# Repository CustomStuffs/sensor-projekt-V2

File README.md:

# Sensor Hub

Outdoor environmental monitoring system built on a Raspberry Pi Pico W. Sensors are read every 30 minutes, uploaded over WiFi to a FastAPI server running on a Raspberry Pi, and displayed in a browser dashboard.

## System overview

```
Pico W (MicroPython)
  └─ POST JSON ──► RPi FastAPI server (port 8080)
                      └─ SQLite DB
                      └─ Static files ──► Browser dashboard
```

Remote access via Tailscale VPN — no port forwarding, no auth layer needed.

## Sensors

| Sensor | Chip / interface | Board connection | Measures |
|--------|-----------------|------------------|----------|
| Temperature | DS18B20, 1-Wire (GP8) | W1 (J2) | °C |
| Humidity | DHT22, GP9 | W2 (J3) | % RH + °C fallback |
| pH | AD8603 buffer → ADS1115 AIN0 (I2C, GP2/3) | BNC (J1), guarded input | pH 0–14 |
| Light | VEML7700, I2C (GP2/3) | on the board, under a light pipe to the lid | lux |
| Soil moisture | Capacitive, Pico ADC (GP26) | J11 solder holes (GP26–28) | % |
| Motion | PIR, GP11 (also wake IRQ), power-gated by GP12 | W3 (J4) | boolean |
| Water level | Float switch, GP16 | W4 (J5) | float |
| Probe temperature | NTC → ADS1115 AIN1 | J8 pins 3/4 | °C (for compensation) |
| EC | **not on the v1 board** (LMP91200 is EOL; firmware driver exists, keep `ec` disabled) | — | µS/cm |

All sensor fields are nullable — unconnected sensors send `null`.

## Relays (two on-board channels)

The PCB carries **two independent SPDT relays** (K1 on GP10, K2 on GP15), rated 230 VAC / 5 A with reinforced insulation to the sensor side, as a hard minimum. Both relays can be switched and scheduled from the dashboard, and local sensor rules can target either one (`"relay": 2` in a rule; default is relay 1). This allows two simultaneous actuator channels (e.g. pump + valve) without external modules. Future board variants can add more relays.

- **Auto rules**: threshold-based (e.g. water when soil < 30 %) configured in `firmware/src/config.json`
- **Schedule**: time-based rules, also in `config.json`
- **Manual override**: one-click from the dashboard, queued via server command API

## Repo layout

```
firmware/   MicroPython source + flash/dev tools
server/     FastAPI app, SQLite schema, systemd unit
dashboard/  Vanilla HTML/JS/CSS frontend
hardware/   KiCad project + generation scripts, BOM, JLCPCB order files
```

Each folder has its own `CLAUDE.md` with subproject-specific rules.

## Getting started

### Firmware

Requires MicroPython 1.28+ (`RPI_PICO_W` build).

```bash
cd firmware
bash tools/setup.sh          # install mpremote, check device
cp src/config.json.example src/config.json   # fill in WiFi + server URL
bash tools/flash.sh          # copy all files to device
bash tools/monitor.sh        # watch serial output
```

For daily development, use the mount workflow instead of reflashing:

```bash
bash tools/mount.sh   # edits in src/ take effect on Ctrl-D
```

### Server

```bash
cd server
pip install -r requirements.txt
uvicorn api.main:app --host 0.0.0.0 --port 8080
```

Or run as a systemd service:

```bash
sudo cp sensor_hub.service /etc/systemd/system/
sudo systemctl enable --now sensor_hub
```

### Dashboard

Served as static files by the FastAPI server — no build step. Open `http://<pi-ip>:8080` in a browser.

### Hardware

100 × 100 mm, 2-layer PCB (`hardware/kicad/`), generated and routed by the scripts in `hardware/tools/`. JLCPCB fabricates the board and places all SMD parts (`hardware/fab/`, regenerate with `python3 hardware/tools/jlc_export.py`); the through-hole parts — Pico WH sockets, relays, Wago push-in terminals, BNC, X2 capacitors, UART header — are hand-soldered. Details: `hardware/CLAUDE.md` and `hardware/docs/`.

## Pico W hardware notes

- **VSYS ADC**: use `ADC(29)` (GPIO29), not `ADC(3)`. On Pico W, GPIO29 is the VSYS/3 voltage divider. `ADC(3)` reads GPIO3 (I2C SCL) and gives garbage.
- **VSYS measurement timing**: read VSYS *before* `wlan.active(True)` — GPIO29 is shared with the WiFi SPI bus and returns wrong values while the radio is up.
- **Lightsleep after WiFi**: `machine.lightsleep(ms)` can fail silently on Pico W after WiFi use. The firmware falls back to `time.sleep()` automatically and logs when this happens.
- **Serial monitor**: uses `mpremote` (`bash tools/monitor.sh`), not minicom. On immutable distros (Bazzite/Silverblue), minicom is not available.
- **Flashing**: the device enters lightsleep ~30 s after boot, making `mpremote` unreachable. Flash immediately after plugging in USB, or interrupt via REPL first.

## Power budget (battery operation)

| State | Current |
|-------|---------|
| Lightsleep | 0.30 mA |
| Sensing (all sensors) | 25 mA |
| WiFi active | 80 mA |
| **Average (30 min cycle)** | **~1.2 mA** |

A 10 000 mAh power bank lasts roughly 6–11 months.

## License

MIT

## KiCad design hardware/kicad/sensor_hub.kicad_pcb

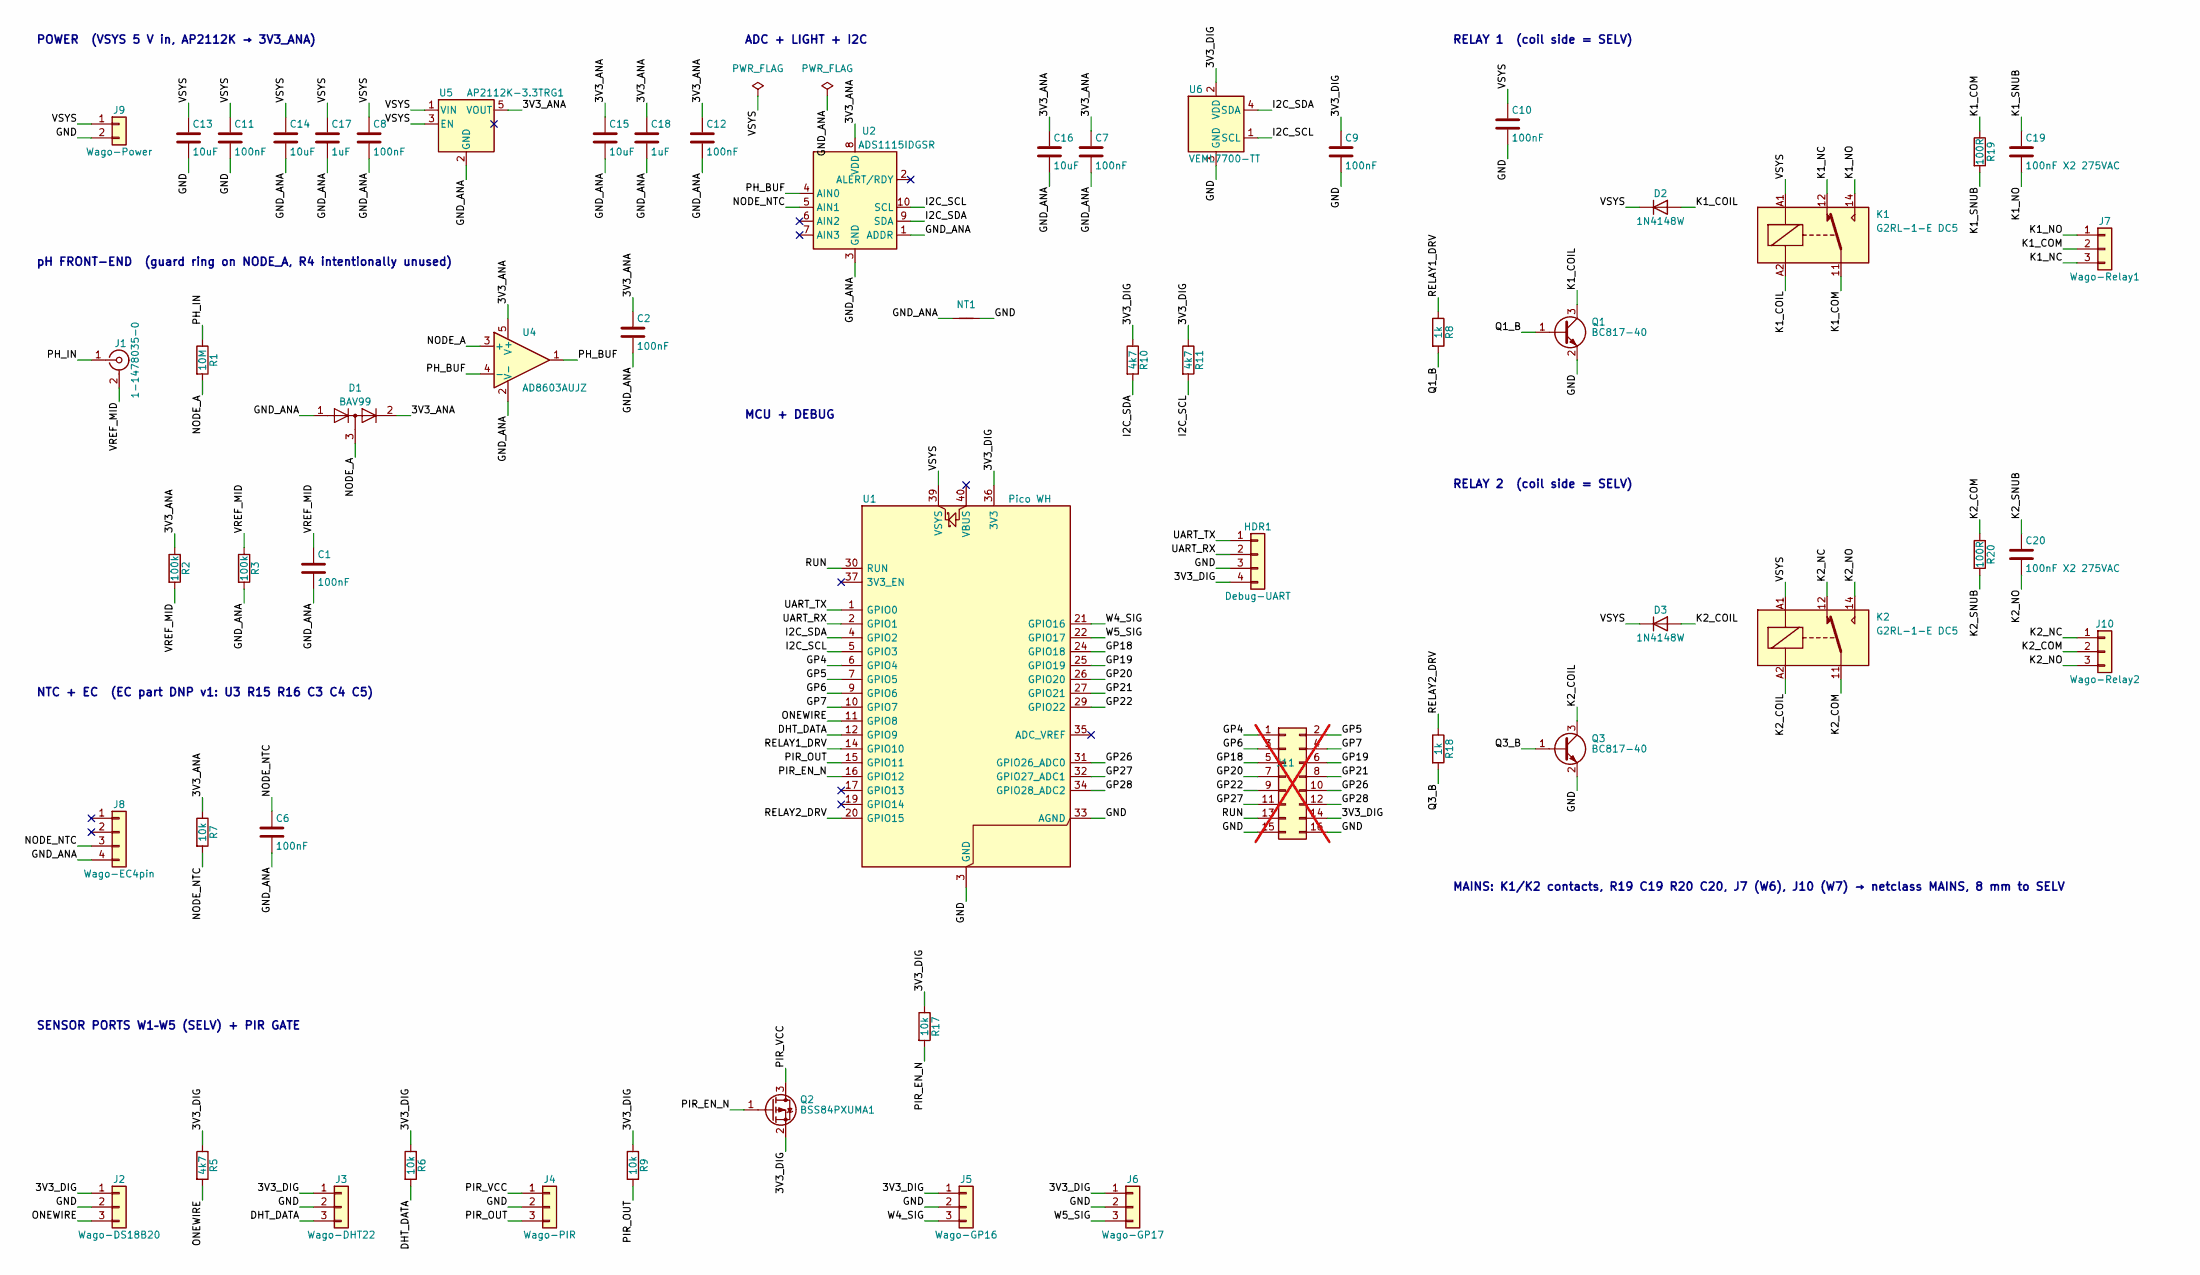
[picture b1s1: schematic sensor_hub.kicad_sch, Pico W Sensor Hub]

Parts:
C1, C2, C6, C7, C8, C9, C10, C11, C12: 100nF; C_0603_1608Metric
C13, C14, C15, C16: 10uF; C_0805_2012Metric
C17, C18: 1uF; C_0603_1608Metric
C19, C20: 100nF X2 275VAC; C_Rect_L13.0mm_W6.0mm_P10.00mm_FKS3_FKP3_MKS4
D1: BAV99; SOT-23
D2, D3: 1N4148W; D_SOD-123
HDR1: Debug-UART; PinHeader_1x04_P2.54mm_Vertical
J1: 1-1478035-0; BNC_TEConnectivity_1478035_Horizontal
J2: Wago-DS18B20; TerminalBlock_WAGO_2601-1103_1x03_P3.50mm_Horizontal
J3: Wago-DHT22; TerminalBlock_WAGO_2601-1103_1x03_P3.50mm_Horizontal
J4: Wago-PIR; TerminalBlock_WAGO_2601-1103_1x03_P3.50mm_Horizontal
J5: Wago-GP16; TerminalBlock_WAGO_2601-1103_1x03_P3.50mm_Horizontal
J6: Wago-GP17; TerminalBlock_WAGO_2601-1103_1x03_P3.50mm_Horizontal
J7: Wago-Relay1; TerminalBlock_WAGO_236-403_1x03_P5.00mm_45Degree
J8: Wago-EC4pin; TerminalBlock_WAGO_2601-1104_1x04_P3.50mm_Horizontal
J9: Wago-Power; TerminalBlock_WAGO_2601-1102_1x02_P3.50mm_Horizontal
J10: Wago-Relay2; TerminalBlock_WAGO_236-403_1x03_P5.00mm_45Degree
J11: Spare-GPIO; PinHeader_2x08_P2.54mm_Vertical; not fitted
K1, K2: G2RL-1-E DC5; Relay_SPDT_Omron_G2RL-1-E
NT1: NetTie_2; NetTie-2_SMD_Pad0.5mm
Q1, Q3: BC817-40; SOT-23
Q2: BSS84PXUMA1; SOT-23
R1: 10M; R_0603_1608Metric
R2, R3: 100k; R_0603_1608Metric
R5, R10, R11: 4k7; R_0603_1608Metric
R6, R7, R9, R17: 10k; R_0603_1608Metric
R8, R18: 1k; R_0603_1608Metric
R19, R20: 100R; R_1206_3216Metric
U1: Pico WH; RaspberryPi_Pico_Common_THT
U2: ADS1115IDGSR; MSOP-10_3x3mm_P0.5mm
U4: AD8603AUJZ; TSOT-23-5
U5: AP2112K-3.3TRG1; SOT-23-5
U6: VEML7700-TT; VEML7700_TT

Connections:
/3V3_ANA: C2.1, C7.1, C12.1, C15.1, C16.1, C18.1, D1.2 (A), R2.1, R7.1, U2.8 (VDD), U4.5 (V+), U5.5 (VOUT)
/3V3_DIG: C9.1, HDR1.4, J2.1, J3.1, J5.1, J6.1, J11.14, Q2.2 (S), R5.1, R6.1, R9.1, R10.1, R11.1, R17.1, U1.36 (3V3), U6.2 (VDD)
/DHT_DATA: J3.3, R6.2, U1.12 (GPIO9)
/GND: C9.2, C10.2, C11.2, C13.2, HDR1.3, J2.2, J3.2, J4.2, J5.2, J6.2, J9.2, J11.15, J11.16, NT1.2, Q1.2 (E), Q3.2 (E), U1.3 (GND), U1.8 (GND), U1.13 (GND), U1.18 (GND), U1.23 (GND), U1.28 (GND), U1.33 (AGND), U1.38 (GND), U6.3 (GND)
/GND_ANA: C1.2, C2.2, C6.2, C7.2, C8.2, C12.2, C14.2, C15.2, C16.2, C17.2, C18.2, D1.1 (K), J8.4, NT1.1, R3.2, U2.1 (ADDR), U2.3 (GND), U4.2 (V-), U5.2 (GND)
/GP4: J11.1, U1.6 (GPIO4)
/GP5: J11.2, U1.7 (GPIO5)
/GP6: J11.3, U1.9 (GPIO6)
/GP7: J11.4, U1.10 (GPIO7)
/GP18: J11.5, U1.24 (GPIO18)
/GP19: J11.6, U1.25 (GPIO19)
/GP20: J11.7, U1.26 (GPIO20)
/GP21: J11.8, U1.27 (GPIO21)
/GP22: J11.9, U1.29 (GPIO22)
/GP26: J11.10, U1.31 (GPIO26_ADC0)
/GP27: J11.11, U1.32 (GPIO27_ADC1)
/GP28: J11.12, U1.34 (GPIO28_ADC2)
/I2C_SCL: R11.2, U1.5 (GPIO3), U2.10 (SCL), U6.1 (SCL)
/I2C_SDA: R10.2, U1.4 (GPIO2), U2.9 (SDA), U6.4 (SDA)
/K1_COIL: D2.2 (A), K1.A2, Q1.3 (C)
/K1_COM: J7.2, K1.11, R19.1
/K1_NC: J7.3, K1.12
/K1_NO: C19.2, J7.1, K1.14
/K1_SNUB: C19.1, R19.2
/K2_COIL: D3.2 (A), K2.A2, Q3.3 (C)
/K2_COM: J10.2, K2.11, R20.1
/K2_NC: J10.1, K2.12
/K2_NO: C20.2, J10.3, K2.14
/K2_SNUB: C20.1, R20.2
/NODE_A: D1.3 (K), R1.2, U4.3 (+)
/NODE_NTC: C6.1, J8.3, R7.2, U2.5 (AIN1)
/ONEWIRE: J2.3, R5.2, U1.11 (GPIO8)
/PH_BUF: U2.4 (AIN0), U4.1, U4.4 (-)
/PH_IN: J1.1 (In), R1.1
/PIR_EN_N: Q2.1 (G), R17.2, U1.16 (GPIO12)
/PIR_OUT: J4.3, R9.2, U1.15 (GPIO11)
/PIR_VCC: J4.1, Q2.3 (D)
/Q1_B: Q1.1 (B), R8.2
/Q3_B: Q3.1 (B), R18.2
/RELAY1_DRV: R8.1, U1.14 (GPIO10)
/RELAY2_DRV: R18.1, U1.20 (GPIO15)
/RUN: J11.13, U1.30 (RUN)
/UART_RX: HDR1.2, U1.2 (GPIO1)
/UART_TX: HDR1.1, U1.1 (GPIO0)
/VREF_MID: C1.1, J1.2 (Ext), R2.2, R3.1
/VSYS: C8.1, C10.1, C11.1, C13.1, C14.1, C17.1, D2.1 (K), D3.1 (K), J9.1, K1.A1, K2.A1, U1.39 (VSYS), U5.1 (VIN), U5.3 (EN)
/W4_SIG: J5.3, U1.21 (GPIO16)
/W5_SIG: J6.3, U1.22 (GPIO17)

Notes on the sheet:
RELAY 1 (coil side = SELV)
ADC + LIGHT + I2C
MCU + DEBUG
NTC + EC (EC part DNP v1: U3 R15 R16 C3 C4 C5)
SENSOR PORTS W1–W5 (SELV) + PIR GATE
pH FRONT-END (guard ring on NODE_A, R4 intentionally unused)
RELAY 2 (coil side = SELV)
MAINS: K1/K2 contacts, R19 C19 R20 C20, J7 (W6), J10 (W7) → netclass MAINS, 8 mm to SELV
POWER (VSYS 5 V in, AP2112K → 3V3_ANA)

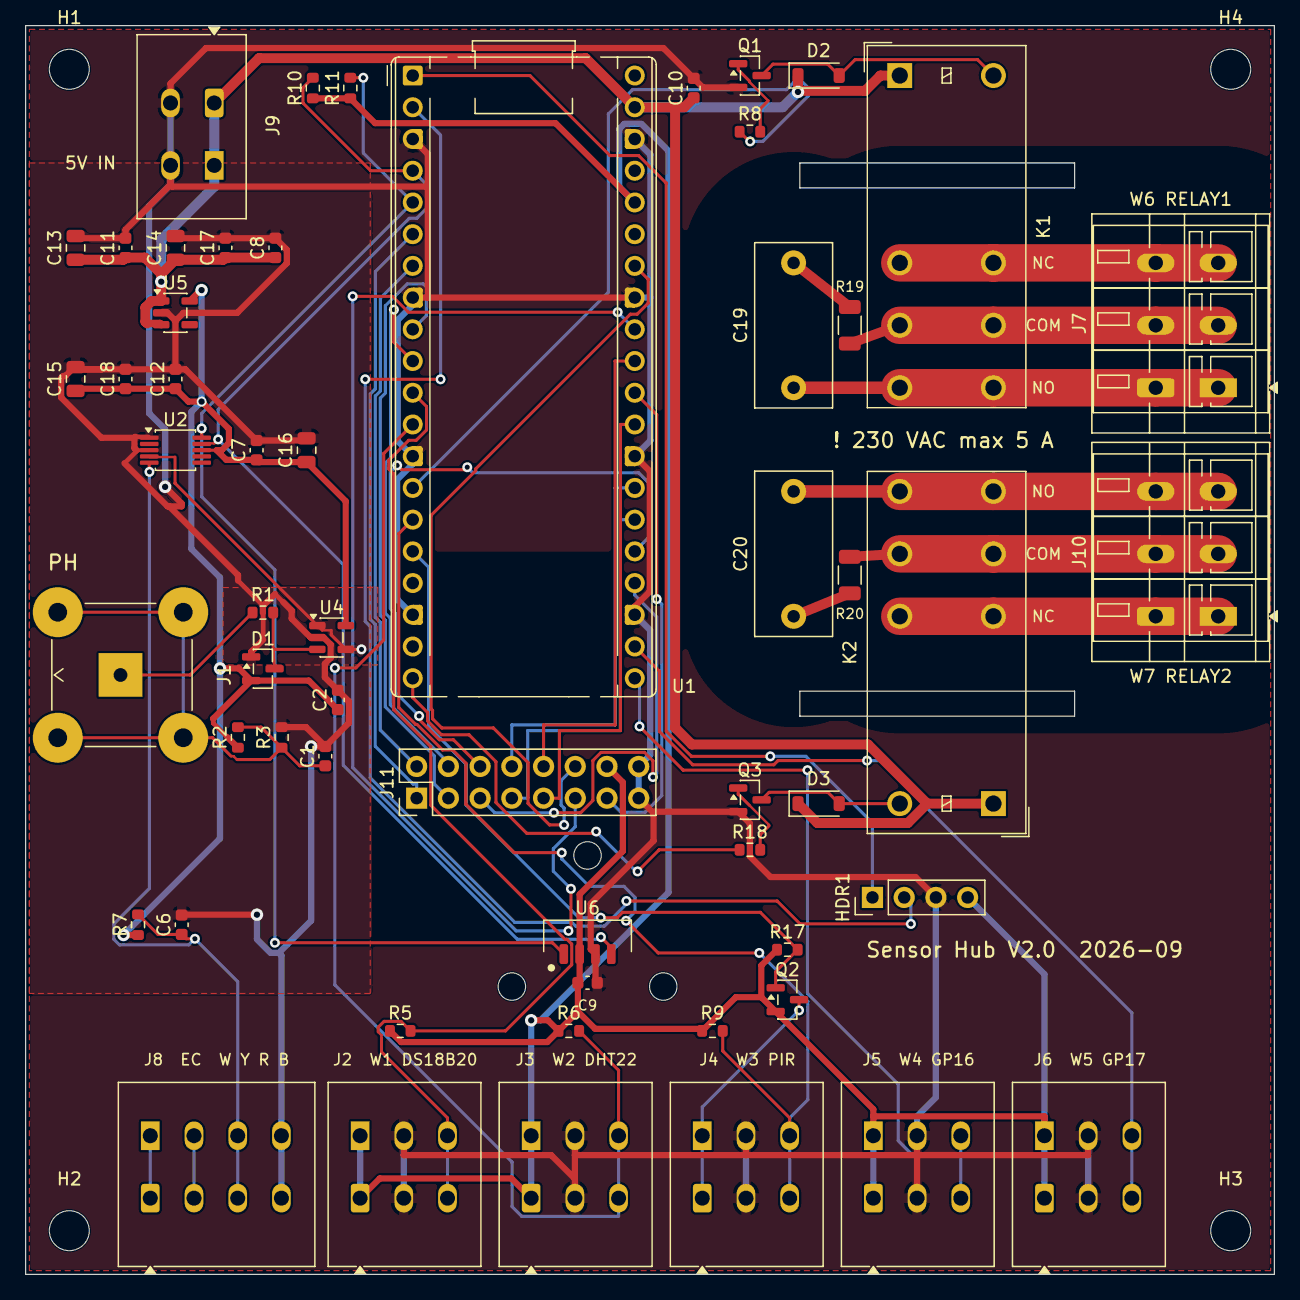
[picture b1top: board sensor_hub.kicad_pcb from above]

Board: 2 copper layers, 100.0 x 100.0 mm, 64 parts (0 on the bottom side), 48 nets.

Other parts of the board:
H1, H2, H3, H4: MountingHole_3.2mm_M3
H5, H6, H7: MountingHole_2.2mm_M2

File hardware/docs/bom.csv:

ref,description,part_number,manufacturer,qty,unit_chf,ext_chf,distributor,notes,lcsc
U1,Raspberry Pi Pico WH (pre-soldered headers),SC0919,Raspberry Pi,1,6.50,6.50,Distrelec / Mouser,Pico W with headers; plugs into U1 sockets; price est.,
U1-SKT,Female header 1x20 2.54mm THT (socket for Pico WH),"generic 1x20 female, 8.5 mm",various,2,0.60,1.20,Distrelec / Mouser,Two sockets for U1 footprint RaspberryPi_Pico_Common_THT; price est.,
U2,16-bit I2C ADC 4ch VSSOP-10,ADS1115IDGSR,Texas Instruments,1,1.50,1.50,Mouser 595-ADS1115IDGSR,I2C addr 0x48 (ADDR to GND),C37593
U4,Op-amp FET-in rail-to-rail TSOT-23-5,AD8603AUJZ-REEL7,Analog Devices,1,1.20,1.20,LCSC / Mouser 584-AD8603AUJZ-REEL7,"pH unity-gain buffer; single supply 3.3V (order code AUJZ = TSOT-23-5; ""ARTZ"" does not exist)",C14937
U5,LDO 3.3V 600mA SOT-23-5,AP2112K-3.3TRG1,Diodes Inc.,1,0.40,0.40,Mouser 621-AP2112K-3.3TRG1,Separate analog 3V3 rail,C51118
D1,Dual series ESD diode SOT-23,BAV99,Nexperia,1,0.10,0.10,Mouser 771-BAV99215,pH input protection (GND / VCC clamp),C2500
D2,Signal diode SOD-123,1N4148W,Vishay,1,0.05,0.05,Mouser 78-1N4148W-E3-08,Relay 1 flyback,C81598
D3,Signal diode SOD-123,1N4148W,Vishay,1,0.05,0.05,Mouser 78-1N4148W-E3-08,Relay 2 flyback,C81598
Q1,NPN BJT SOT-23,BC817-40,ON Semiconductor,1,0.10,0.10,Mouser 512-BC817-40LT1G,Relay 1 driver,C52801
Q3,NPN BJT SOT-23,BC817-40,ON Semiconductor,1,0.10,0.10,Mouser 512-BC817-40LT1G,Relay 2 driver,C52801
K1,SPDT relay 5V coil 16A PCB mount reinforced,G2RL-1-E DC5,Omron,1,2.50,2.50,Mouser 653-G2RL-1-E-DC5,5V coil ≈80 mA from VSYS; 16 A 250 VAC; 5 kVAC reinforced coil-contact (required for 230 VAC next to SELV); price est.,
K2,SPDT relay 5V coil 16A PCB mount reinforced,G2RL-1-E DC5,Omron,1,2.50,2.50,Mouser 653-G2RL-1-E-DC5,Second on-board relay (minimum requirement); same part as K1,
J1,BNC female right-angle PCB mount 50 Ohm,1-1478035-0,TE Connectivity,1,2.50,2.50,Mouser / Distrelec,pH sensor connector; shell = shield = VREF_MID (not GND); KiCad footprint BNC_TEConnectivity_1478035_Horizontal; price est.,
J2-J6,Wago 3-pole push-in PCB terminal 3.5mm pitch (SELV sensors),2601-1103,Wago,5,0.90,4.50,Distrelec / Wago direct,Sensor ports W1-W5 (SELV side only); price est.,
J7 J10,Wago 3-pole CAGE CLAMP PCB terminal 5mm pitch 45°,236-403,Wago,2,1.20,2.40,Distrelec / Wago direct,Relay ports W6 = J7 (K1) + W7 = J10 (K2) in MAINS zone; 2.5 mm²; 24 A (IEC) / 300 V 15 A (UL); price est.,
J8,Wago 4-pole push-in PCB terminal 3.5mm pitch,2601-1104,Wago,1,1.10,1.10,Distrelec / Wago direct,NTC probe on pins 3-4 (EC pins 1-2 unused in v1); same 2601 family as J2-J6 (was Phoenix screw terminal); price est.,
R1,Resistor 10M 0603 1%,RC0603FR-0710ML,Yageo,1,0.05,0.05,Mouser 603-RC0603FR-0710ML,pH series input (BNC center → NODE_A); inside guard ring,C7250
R2-R3,Resistor 100k 0603 1%,RC0603FR-07100KL,Yageo,2,0.02,0.04,Mouser 603-RC0603FR-07100KL,VREF divider (NODE_VREF); R4 intentionally unused,C25803
R6 R7 R9 R17,Resistor 10k 0603 1%,RC0603FR-0710KL,Yageo,4,0.02,0.08,Mouser 603-RC0603FR-0710KL,R6 DHT22 pull-up; R7 NTC pull-up; R9 PIR out pull-up; R17 BSS84 gate pull-up,C25804
R5 R10 R11,Resistor 4.7k 0603 1%,RC0603FR-074K7L,Yageo,3,0.02,0.06,Mouser 603-RC0603FR-074K7L,R5 1-Wire pull-up; R10/R11 I2C pull-ups,C23162
R8 R18,Resistor 1k 0603 1%,RC0603FR-071KL,Yageo,2,0.02,0.04,Mouser 603-RC0603FR-071KL,"Relay base drive (R8 → Q1, R18 → Q3)",C21190
R19-R20,Resistor 100R 1206 1%,RC1206FR-07100RL,Yageo,2,0.05,0.10,Mouser 603-RC1206FR-07100RL,Relay contact snubber resistors (series with C19/C20); 1206 for mains (200 V working),C17901
C1-C2 C6-C12,Cap 100nF 0603 X7R 25V,GRM188R71E104KA01D,Murata,9,0.05,0.45,Mouser 81-GRM188R71E104KA1D,C1 VREF; C2 AD8603; C6 NTC; C7 ADS1115; C8 LDO in; C9 VEML7700; C10 relay coils; C11 VSYS entry; C12 LDO out,C14663
C13-C16,Cap 10uF 0805 X5R 10V (25V part fitted by JLC),GRM21BR61A106KE18L,Murata,4,0.10,0.40,Mouser 81-GRM21BR61A106KE8L,10 µF bulk: C13 VSYS entry; C14 LDO in; C15 LDO out; C16 ADS1115 VDD,C15850
C17-C18,Cap 1uF 0603 X5R 10V,GRM188R61A105KA61D,Murata,2,0.08,0.16,Mouser 81-GRM188R61A105KA61D,AP2112K input (C17) / output (C18),C15849
C19-C20,Cap 100nF X2 film 275VAC THT,"X2 film 100nF 275VAC, 13x6 mm body, 10 mm pitch (e.g. WIMA MKX2)",Vishay / KEMET,2,0.40,0.80,Mouser,Relay contact EMC snubbers (series with R19/R20); X2 mandatory (230 VAC); DNP per channel for LED/contactor loads; footprint C_Rect_L13.0mm_W6.0mm_P10.00mm — verify body size of chosen part,
PCB,"2-layer FR4 ENIG 100x100mm, SMD assembly top side (qty 5)",Custom,JLCPCB,1,1.50,1.50,jlcpcb.com,"JLCPCB fab + SMD assembly: run tools/jlc_export.py, upload fab/gerbers.zip + bom_jlc.csv + cpl_jlc.csv",
HDR1,2.54mm 1x4 debug header,PEC04SAAN,Sullins,1,0.20,0.20,Mouser 538-22-28-4040,UART0 TX RX + GND + 3V3,
U6,Ambient light sensor I2C 4-pin 6.8x2.35x3.0mm top view,VEML7700-TT,Vishay,1,0.80,0.80,Mouser 782-VEML7700-TT,I2C addr 0x10 (fixed). Footprint sensor_hub:VEML7700_TT (datasheet 84286 p.10),C1850416
Q2,P-channel MOSFET SOT-23,BSS84PXUMA1,Infineon,1,0.10,0.10,Mouser 771-BSS84PXUMA1,PIR power gate (GP12); Vgs(th) -0.8 to -2.5V; Id -130mA; source→3V3_DIG drain→PIR VCC,C152212
J9,Wago 2-pole push-in PCB terminal 3.5mm pitch,2601-1102,Wago,1,0.70,0.70,Distrelec / Wago direct,VSYS + GND PCB-side input (was Phoenix screw terminal); connects to Bulgin PX0441 panel connector via short cable; price est.,
,,,,,,,,,
,,TOTAL,,,,31.08,,Excluding enclosure and cable glands; DNP items at 0.00; two 230 VAC relays + 7× Wago + X2 snubbers,

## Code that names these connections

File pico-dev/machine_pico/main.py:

"""
Machine Pico — UART bridge + relay controller
Wiring: UART1 TX=GPIO4 → Project Pico RX=GPIO1
        UART1 RX=GPIO5 ← Project Pico TX=GPIO0
        GPIO15 → Relay1 IN  (LOW = relay closed = RUN pulled to GND = reset)
        GPIO28 → Relay2 IN  (LOW = relay closed = light ON)

Commands (normal mode):
  RESET         — pulse relay1 100 ms → hard-reset Project Pico
  SEND:<text>   — write <text>\\r\\n to Project Pico via UART
  BRIDGE        — enter transparent passthrough mode (USB ↔ UART1)
  LIGHT_ON      — close light relay (GPIO28 LOW)
  LIGHT_OFF     — open light relay (GPIO28 HIGH)
  LIGHT_TOGGLE  — toggle light relay

Bridge mode:
  All USB bytes are forwarded to UART1 and vice versa with no processing.
  This lets mpremote (or any tool) talk directly to the Project Pico's
  UART0 REPL. Exit by sending 5× Ctrl-C in a row.
"""
import machine
import utime
import sys
import uselect
import micropython

BAUD     = 115200
RESET_MS = 100

uart  = machine.UART(1, baudrate=BAUD, tx=machine.Pin(4), rx=machine.Pin(5))
relay = machine.Pin(15, machine.Pin.OUT, value=1)
light = machine.Pin(28, machine.Pin.OUT, value=1)   # active-LOW; 1 = off

_poll = uselect.poll()
_poll.register(sys.stdin, uselect.POLLIN)


def relay_reset(ms=RESET_MS):
    relay.value(0)
    utime.sleep_ms(ms)
    relay.value(1)


def usb_write(msg):
    sys.stdout.write(msg)


# ── Bridge mode ───────────────────────────────────────────────────────────────

def run_bridge():
    """
    Transparent USB↔UART passthrough. mpremote can connect to this port and
    talk directly to the Project Pico's UART0 REPL (Pico W default primary
    REPL stream). Exit: send 5× Ctrl-C in a row.
    """
    usb_write("[bridge] BRIDGE MODE — 5x Ctrl-C to exit\r\n")

    # Disable MicroPython's own Ctrl-C interrupt so we can forward \x03 raw.
    micropython.kbd_intr(-1)

    exit_count = 0

    try:
        while True:
            # UART → USB: forward Project Pico output
            n = uart.any()
            if n:
                chunk = uart.read(n)
                # latin-1: lossless 1-to-1 byte↔char mapping for raw bytes
                sys.stdout.write(chunk.decode("latin-1"))

            # USB → UART: forward mpremote / tool input
            if _poll.poll(0):
                try:
                    ch = sys.stdin.read(1)
                except UnicodeError:
                    continue
                uart.write(ch.encode("latin-1"))

                if ch == "\x03":          # Ctrl-C
                    exit_count += 1
                    if exit_count >= 5:
                        break
                else:
                    exit_count = 0

            utime.sleep_ms(1)
    finally:
        micropython.kbd_intr(3)           # re-enable Ctrl-C
        usb_write("\r\n[bridge] bridge mode ended\r\n")


# ── Normal command mode ───────────────────────────────────────────────────────

usb_write("[bridge] ready — RESET | SEND:<text> | BRIDGE | LIGHT_ON | LIGHT_OFF | LIGHT_TOGGLE\r\n")

_cmd_buf = ""

while True:
    # Forward Project Pico UART output → USB
    n = uart.any()
    if n:
        chunk = uart.read(n)
        usb_write(chunk.decode("latin-1"))

    # Read USB commands (non-blocking)
    if _poll.poll(0):
        try:
            ch = sys.stdin.read(1)
        except UnicodeError:
            continue

        if ch in ("\r", "\n"):
            cmd = _cmd_buf.strip()
            _cmd_buf = ""

            if not cmd:
                pass

            elif cmd == "RESET":
                relay_reset()
                usb_write("[bridge] RESET sent\r\n")

            elif cmd.startswith("SEND:"):
                payload = cmd[5:]
                uart.write(payload + "\r\n")
                usb_write("[bridge] TX: " + payload + "\r\n")

            elif cmd == "BRIDGE":
                run_bridge()

            elif cmd == "LIGHT_ON":
                light.value(0)
                usb_write("[bridge] light ON\r\n")

            elif cmd == "LIGHT_OFF":
                light.value(1)
                usb_write("[bridge] light OFF\r\n")

            elif cmd == "LIGHT_TOGGLE":
                light.value(1 - light.value())
                usb_write("[bridge] light " + ("ON" if light.value() == 0 else "OFF") + "\r\n")

            else:
                usb_write("[bridge] unknown: " + cmd + "\r\n")

        else:
            _cmd_buf += ch

    utime.sleep_ms(1)
